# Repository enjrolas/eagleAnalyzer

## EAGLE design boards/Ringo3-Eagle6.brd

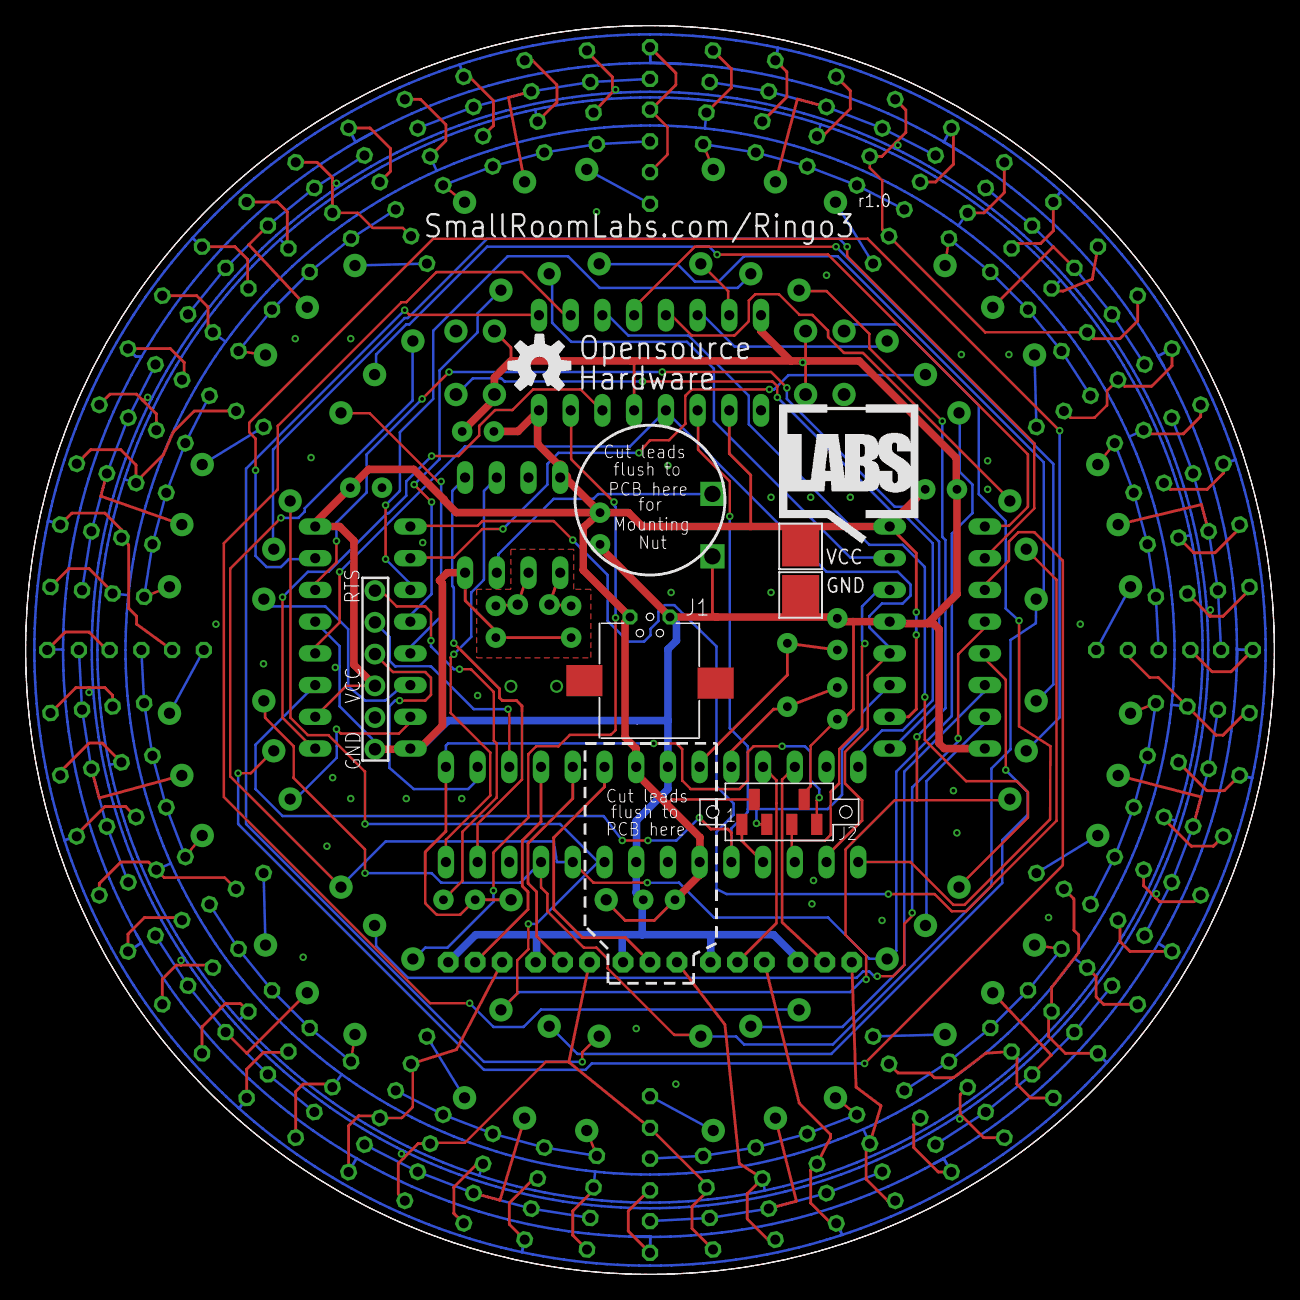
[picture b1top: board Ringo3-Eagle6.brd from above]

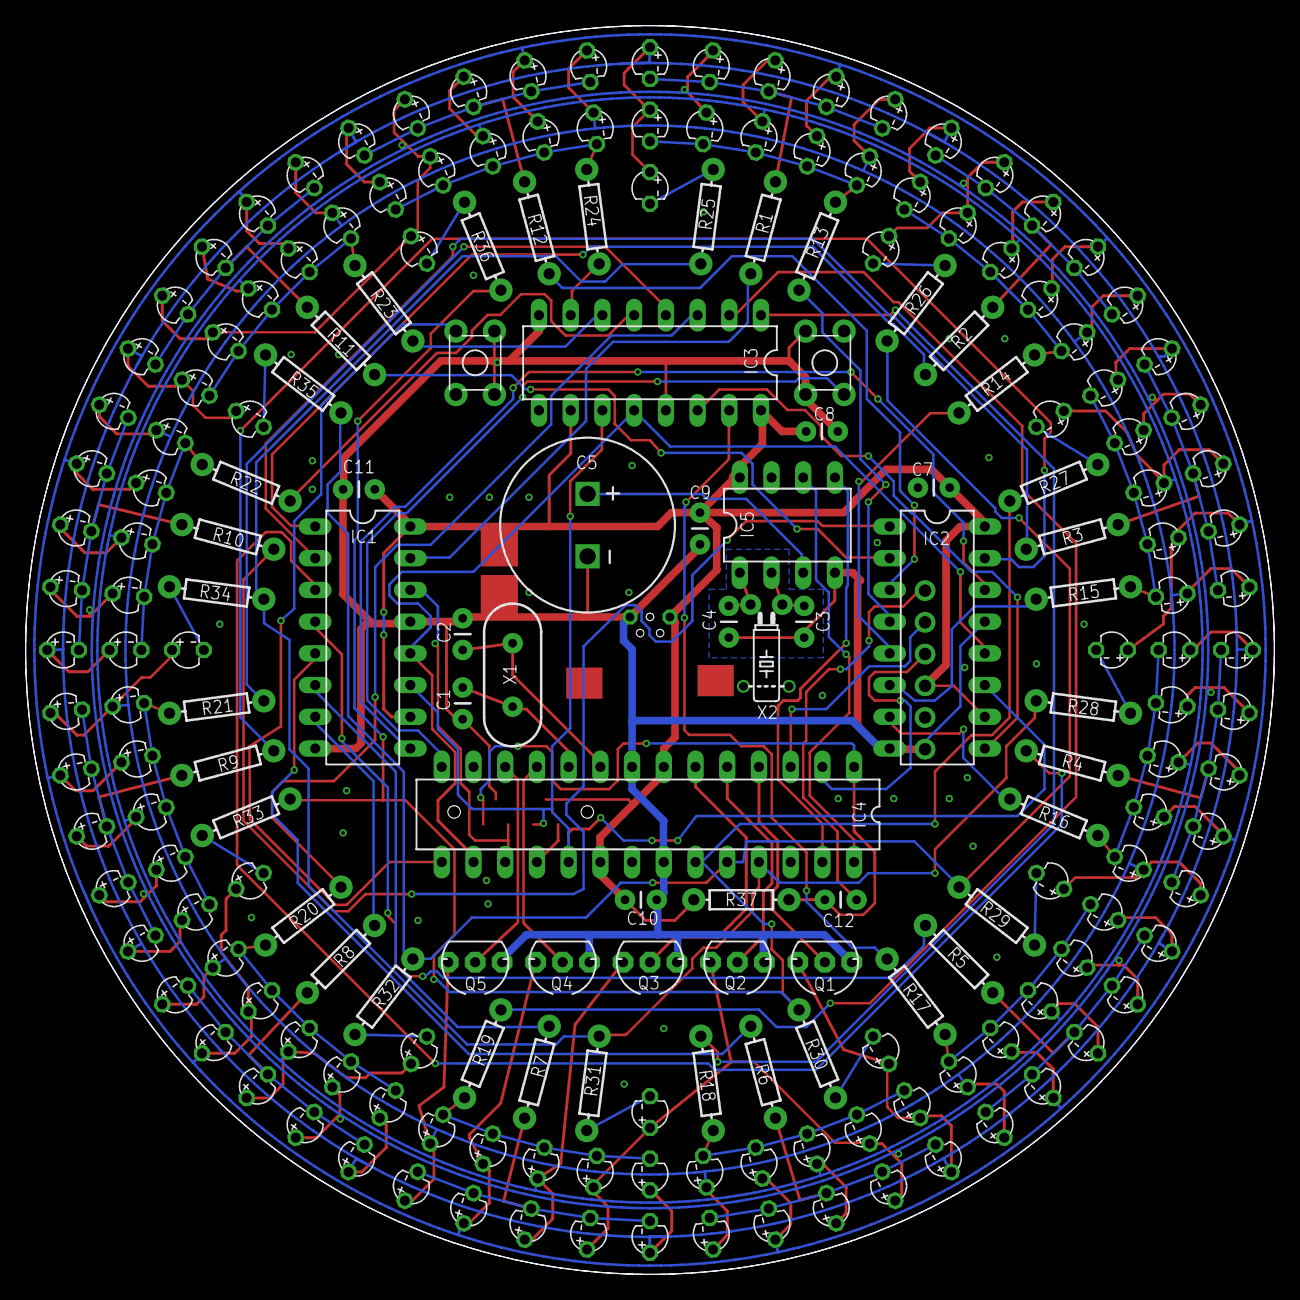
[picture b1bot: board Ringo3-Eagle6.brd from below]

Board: 2 copper layers, 100.0 x 100.0 mm, 199 parts (194 on the bottom side), 94 nets.

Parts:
C1, C2, C3, C4, C7, C8, C9, C10, C11, C12: CAP-PTH-SMALL
C5: CAPPOLSUPER13/5; CAP-SUPER13/5
CN1: 1X06_ROUND
D1, D2, D3, D4, D5, D6, D7, D8, D9, D10, D11, D12, D13, D14, D15, D16, D17, D18, D19, D20, D21, D22, D23, D24, D25, D26, D27, D28, D29, D30, D31, D32, D33, D34, D35, D36, D37, D38, D39, D40, D41, D42, D43, D44, D45, D46, D47, D48, D49, D50, D51, D52, D53, D54, D55, D56, D57, D58, D59, D60, D61, D62, D63, D64, D65, D66, D67, D68, D69, D70, D71, D72, D73, D74, D75, D76, D77, D78, D79, D80, D81, D82, D83, D84, D85, D86, D87, D88, D89, D90, D91, D92, D93, D94, D95, D96, D97, D98, D99, D100, D101, D102, D103, D104, D105, D106, D107, D108, D109, D110, D111, D112, D113, D114, D115, D116, D117, D118, D119, D120, D121, D122, D123, D124, D125, D126, D127, D128, D129, D130, D131, D132: LED3MM
IC1, IC2, IC3: 74HCT595N; DIL16
IC4: MEGA8-P; DIL28-3
IC5: MCP79410DIL; DIL08-LONG
J1: USB-PWRPAD; USB-MINIB-PTH-PWR-PAD
J2: AVR-ISP6_TOUCH; ISP-TOUCH
Q1, Q2, Q3, Q4, Q5: N-FETSTR; TO92-STRAIGHT
R1, R2, R3, R4, R5, R6, R7, R8, R9, R10, R11, R12, R13, R14, R15, R16, R17, R18, R19, R20, R21, R22, R23, R24, R25, R26, R27, R28, R29, R30, R31, R32, R33, R34, R35, R36, R37: AXIAL-0.3
U$17, U$18: TACTILETACT-4.5X4.5-PTH; TACTILE-PTH-4.5X4.5
U$21: OSHW-LOGO-M
U$22: SRL-LOGO-SILK-10MM
X1: HC49US
X2: TC26H

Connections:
AN1: IC1.15, R1.P$1
AN2: IC1.1, R2.P$1
AN3: IC1.2, R3.P$1
AN4: IC1.3, R4.P$1
AN5: IC1.4, R5.P$1
AN6: IC1.5, R6.P$1
AN7: IC1.6, R7.P$1
AN8: IC1.7, R8.P$1
AN9: IC2.15, R9.P$1
AN10: IC2.1, R10.P$1
AN11: IC2.2, R11.P$1
AN12: IC2.3, R12.P$1
AN13: IC2.4, R13.P$1
AN14: IC2.5, R14.P$1
AN15: IC2.6, R15.P$1
AN16: IC2.7, R16.P$1
AN17: IC3.15, R17.P$1
AN18: IC3.1, R18.P$1
AN19: IC3.2, R19.P$1
AN20: IC3.3, R20.P$1
AN21: IC3.4, R21.P$1
AN22: IC3.5, R22.P$1
AN23: IC3.6, R23.P$1
AN24: IC3.7, R24.P$1
AN25: IC4.25, R25.P$1, R28.P$1, R31.P$1, R34.P$1
AN26: IC4.24, R26.P$1, R29.P$1, R32.P$1, R35.P$1
AN27: IC4.23, R27.P$1, R30.P$1, R33.P$1, R36.P$1
AVR-RX: CN1.4, IC4.2
AVR-TX: CN1.5, IC4.3
BUTTON1: IC4.14, U$17.2A
BUTTON2: IC4.15, U$18.2A
CA1: IC4.4, Q1.2
CA1-BUS: D1.A, D6.A, D11.A, D16.A, D21.A, D26.A, D31.A, D36.A, D41.A, D46.A, D51.A, D56.A, D61.A, D66.A, D71.A, D76.A, D81.A, D86.A, D91.A, D96.A, D101.A, D106.A, D111.A, D116.A, D121.A, D126.A, D131.A, Q1.3
CA2: IC4.5, Q2.2
CA2-BUS: D2.A, D7.A, D12.A, D17.A, D22.A, D27.A, D32.A, D37.A, D42.A, D47.A, D52.A, D57.A, D62.A, D67.A, D72.A, D77.A, D82.A, D87.A, D92.A, D97.A, D102.A, D107.A, D112.A, D117.A, D122.A, D127.A, D132.A, Q2.3
CA3: IC4.6, Q3.2
CA3-BUS: D3.A, D8.A, D13.A, D18.A, D23.A, D28.A, D33.A, D38.A, D43.A, D48.A, D53.A, D58.A, D63.A, D68.A, D73.A, D78.A, D83.A, D88.A, D93.A, D98.A, D103.A, D108.A, D113.A, D118.A, D123.A, D128.A, Q3.3
CA4: IC4.11, Q4.2
CA4-BUS: D4.A, D9.A, D14.A, D19.A, D24.A, D29.A, D34.A, D39.A, D44.A, D49.A, D54.A, D59.A, D64.A, D69.A, D74.A, D79.A, D84.A, D89.A, D94.A, D99.A, D104.A, D109.A, D114.A, D119.A, D124.A, D129.A, Q4.3
CA5: IC4.12, Q5.2
CA5-BUS: D5.A, D10.A, D15.A, D20.A, D25.A, D30.A, D35.A, D40.A, D45.A, D50.A, D55.A, D60.A, D65.A, D70.A, D75.A, D80.A, D85.A, D90.A, D95.A, D100.A, D105.A, D110.A, D115.A, D120.A, D125.A, D130.A, Q5.3
DATA1: IC1.9, IC2.14
DATA2: IC2.9, IC3.14
GND: C1.2, C2.2, C3.2, C4.2, C5.C, C7.2, C8.2, C9.2, C10.2, C11.2, CN1.1, IC1.8, IC1.13, IC2.8, IC2.13, IC3.8, IC3.13, IC4.8, IC4.22, IC5.4, J1.GND, J2.6, Q1.1, Q2.1, Q3.1, Q4.1, Q5.1, U$17.1A, U$17.1B, U$18.1A, U$18.1B
LATCH: IC1.12, IC2.12, IC3.12, IC4.16
MISO: IC4.18, J2.1
MOSI: IC1.14, IC4.17, J2.4
unnamed: D1.C, D2.C, D3.C, D4.C, D5.C, R1.P$2
unnamed: D6.C, D7.C, D8.C, D9.C, D10.C, R2.P$2
unnamed: D21.C, D22.C, D23.C, D24.C, D25.C, R5.P$2
unnamed: D26.C, D27.C, D28.C, D29.C, D30.C, R6.P$2
unnamed: D31.C, D32.C, D33.C, D34.C, D35.C, R7.P$2
unnamed: D36.C, D37.C, D38.C, D39.C, D40.C, R8.P$2
unnamed: D11.C, D12.C, D13.C, D14.C, D15.C, R3.P$2
unnamed: D16.C, D17.C, D18.C, D19.C, D20.C, R4.P$2
unnamed: D41.C, D42.C, D43.C, D44.C, D45.C, R9.P$2
unnamed: D46.C, D47.C, D48.C, D49.C, D50.C, R10.P$2
unnamed: D51.C, D52.C, D53.C, D54.C, D55.C, R11.P$2
unnamed: D56.C, D57.C, D58.C, D59.C, D60.C, R12.P$2
unnamed: D116.C, D117.C, D118.C, D119.C, D120.C, R24.P$2
unnamed: D111.C, D112.C, D113.C, D114.C, D115.C, R23.P$2
unnamed: D106.C, D107.C, D108.C, D109.C, D110.C, R22.P$2
unnamed: D101.C, D102.C, D103.C, D104.C, D105.C, R21.P$2
unnamed: D96.C, D97.C, D98.C, D99.C, D100.C, R20.P$2
unnamed: C3.1, IC5.2, X2.1
unnamed: D91.C, D92.C, D93.C, D94.C, D95.C, R19.P$2
unnamed: D86.C, D87.C, D88.C, D89.C, D90.C, R18.P$2
unnamed: D66.C, D67.C, D68.C, D69.C, D70.C, R14.P$2
unnamed: D71.C, D72.C, D73.C, D74.C, D75.C, R15.P$2
unnamed: D76.C, D77.C, D78.C, D79.C, D80.C, R16.P$2
unnamed: D81.C, D82.C, D83.C, D84.C, D85.C, R17.P$2
unnamed: D61.C, D62.C, D63.C, D64.C, D65.C, R13.P$2
unnamed: C4.1, IC5.1, X2.2
unnamed: C12.2, CN1.6
unnamed: C5.A, IC5.3
unnamed: D121.C, R25.P$2
unnamed: D122.C, R26.P$2
unnamed: D123.C, R27.P$2
unnamed: D124.C, R28.P$2
unnamed: D125.C, R29.P$2
unnamed: D126.C, R30.P$2
unnamed: D127.C, R31.P$2
unnamed: D128.C, R32.P$2
unnamed: D129.C, R33.P$2
unnamed: D130.C, R34.P$2
unnamed: D131.C, R35.P$2
unnamed: D132.C, R36.P$2
RESET: C12.1, IC4.1, J2.5, R37.P$2
SCK: IC1.11, IC2.11, IC3.11, IC4.19, J2.3
SCL: IC4.28, IC5.6
SDA: IC4.27, IC5.5
VCC: C7.1, C8.1, C9.1, C10.1, C11.1, CN1.3, IC1.10, IC1.16, IC2.10, IC2.16, IC3.10, IC3.16, IC4.7, IC4.20, IC5.8, J1.VBUS, J2.2, R37.P$1
XTAL1: C2.1, IC4.9, X1.2
XTAL2: C1.1, IC4.10, X1.1

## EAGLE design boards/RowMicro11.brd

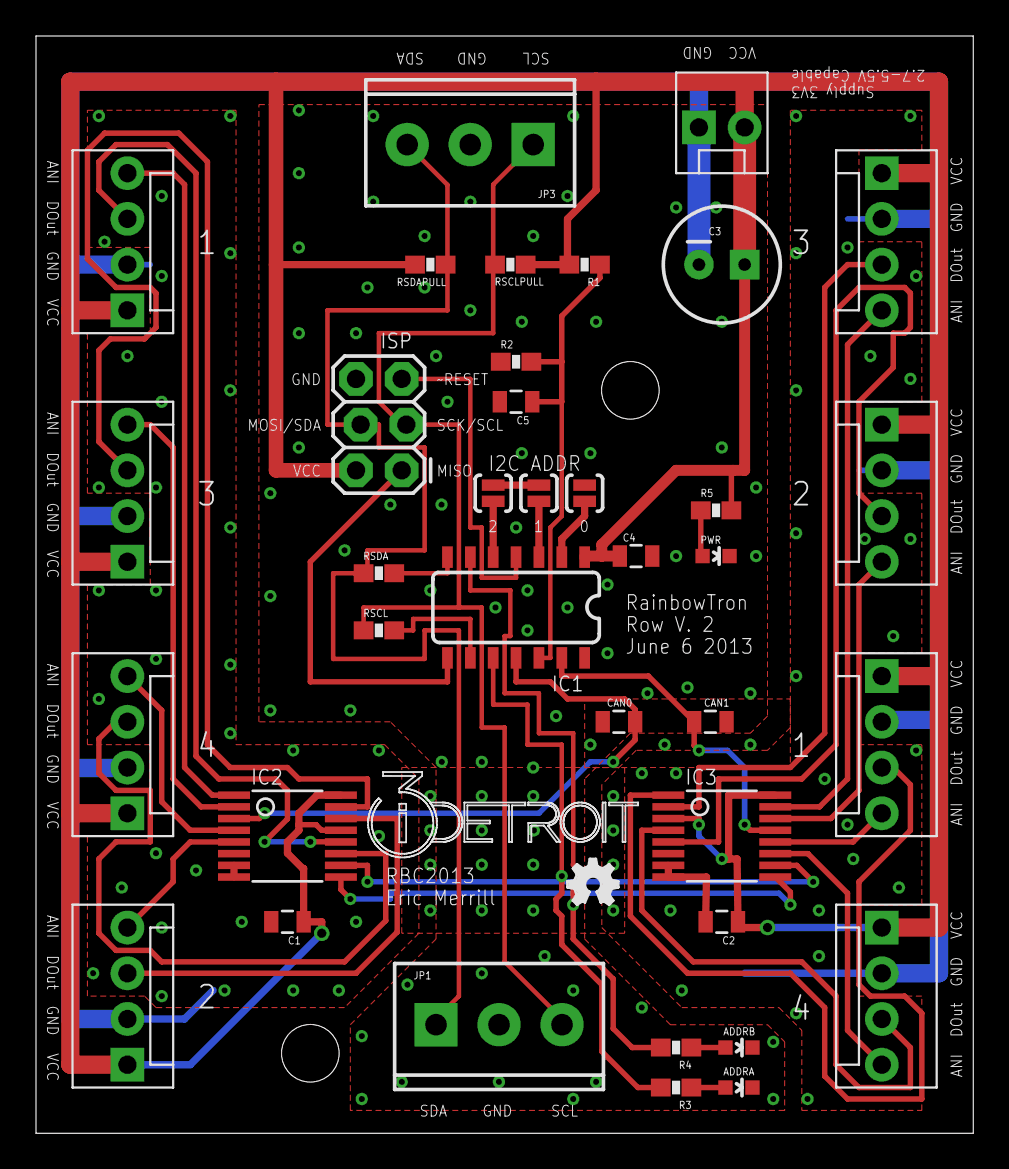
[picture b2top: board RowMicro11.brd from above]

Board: 2 copper layers, 52.1 x 61.0 mm, 39 parts (0 on the bottom side), 35 nets.

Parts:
ADDRA: LED-0603
ADDRB: LED-0603
C1, C2, C4: .1uF; 0805
C3: CPOL-RADIAL-100UF-25V
C5: 10uF; 0805
CAN0, CAN1: 1uF; 0805
IC1: ATTINY84; SO14
IC2, IC3: 74LV4052; TSSOP16L
ISP: 2X3_LOCK
JP1, JP3: SCREWTERMINAL-3.5MM-3
JP2: MOLEX-1X2
JP9, JP10, JP11, JP12, JP13, JP14, JP15, JP16: MOLEX-1X4
PWR: LED-0603
R1: 2.55kΩ; 0603-RES
R2: 5.1kΩ; 0603-RES
R3, R4, R5: 150Ω; 0603-RES
RSCL: 200Ω; 0603-RES
RSCLPULL: 0603-RES
RSDA: 200Ω; 0603-RES
RSDAPULL: 0603-RES
SJ3: 0; SJ_2S-NO
SJ4: 1; SJ_2S-NO
SJ5: 2; SJ_2S-NO
U$1: I3DETROITVEC15MM
U$2: OSHW_FILLX100_NOTEXT

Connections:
ADDRA: IC1.10, IC2.10, IC3.10, R3.2
ADDRB: IC1.6, IC2.9, IC3.9, R4.2
AIN_L1: IC2.1, JP9.4
AIN_L2: IC2.5, JP10.4
AIN_L3: IC2.2, JP11.4
AIN_L4: IC2.4, JP12.4
AIN_R1: IC3.12, JP13.4
AIN_R2: IC3.14, JP14.4
AIN_R3: IC3.15, JP15.4
AIN_R4: IC3.11, JP16.4
DOUT_L1: IC2.12, JP9.3
DOUT_L2: IC2.14, JP10.3
DOUT_L3: IC2.15, JP11.3
DOUT_L4: IC2.11, JP12.3
DOUT_R1: IC3.1, JP13.3
DOUT_R2: IC3.5, JP14.3
DOUT_R3: IC3.2, JP15.3
DOUT_R4: IC3.4, JP16.3
GND: ADDRA.C, ADDRB.C, C1.2, C2.2, C3.2, C4.2, C5.2, CAN0.2, CAN1.2, IC1.14, IC2.6, IC2.7, IC2.8, IC3.6, IC3.7, IC3.8, ISP.6, JP1.2, JP2.1, JP3.2, JP9.2, JP10.2, JP11.2, JP12.2, JP13.2, JP14.2, JP15.2, JP16.2, PWR.C, R2.1, SJ3.2, SJ4.2, SJ5.2
I2CADDR0: IC1.2, SJ3.1
I2CADDR1: IC1.3, SJ4.1
I2CADDR2: IC1.5, SJ5.1
MISO: IC1.8, ISP.1
unnamed: ADDRA.A, R3.1
unnamed: ADDRB.A, R4.1
unnamed: C5.1, IC1.12, R1.1, R2.2
unnamed: CAN0.1, IC1.11, IC2.3
unnamed: IC1.9, RSCL.2
unnamed: PWR.A, R5.1
unnamed: CAN1.1, IC1.13, IC3.13
unnamed: IC1.7, RSDA.2
RESET: IC1.4, ISP.5
SCL: ISP.3, JP1.3, JP3.1, RSCL.1, RSCLPULL.1
SDA: ISP.4, JP1.1, JP3.3, RSDA.1, RSDAPULL.1
VCC: C1.1, C2.1, C3.1, C4.1, IC1.1, IC2.13, IC2.16, IC3.3, IC3.16, ISP.2, JP2.2, JP9.1, JP10.1, JP11.1, JP12.1, JP13.1, JP14.1, JP15.1, JP16.1, R1.2, R5.2, RSCLPULL.2, RSDAPULL.2

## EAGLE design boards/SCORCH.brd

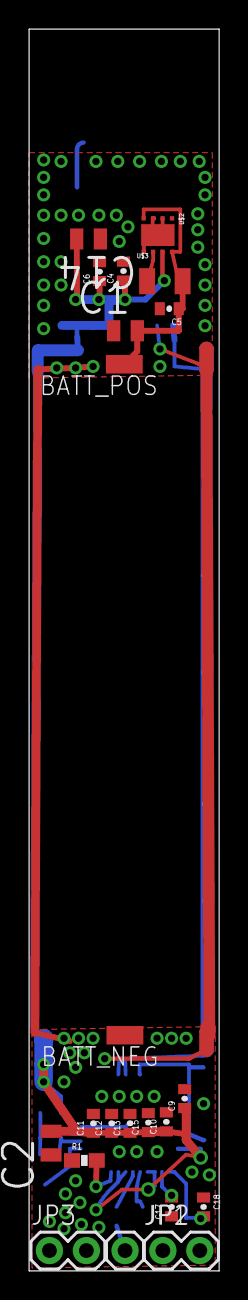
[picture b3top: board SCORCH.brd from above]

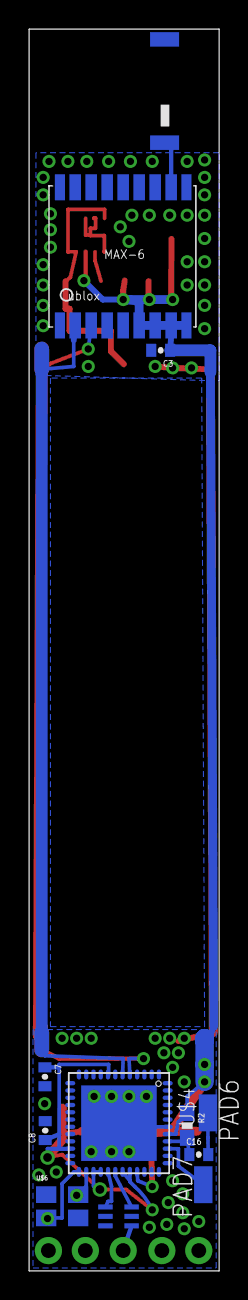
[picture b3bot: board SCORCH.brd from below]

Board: 2 copper layers, 13.1 x 85.4 mm, 34 parts (12 on the bottom side), 16 nets.

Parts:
BATT_NEG: SMD1,27-2,54
BATT_POS: SMD1,27-2,54
C1, C2, C14: 22uF; CAPC2013X90N
C3: 100n; 0402-CAP
C4, C5, C6, C7, C8, C9, C10, C11, C12, C13, C15: 100nF; 0402-CAP
C16: 2.2n; 0402-CAP
C17, C18: 12pF; 0402-CAP
JP1: M01PTH; 1X01
JP2, JP3: 1X02
PAD6, PAD7: WIREPADSMD1,27-254; SMD1,27-2,54
R1: 56K; 0603-RES
R2: 47K; 0603-RES
U$1: UBLOX_MAX-6
U$2: MAX1947MAX1947; 8QFN
U$3: SPM6530SPM6530; INDUCTOR
U$4: CC430F513X---RGZ48; RGZ48
U$5: BALUN433; BALUN
U$6: XTAL26A26; XTAL26
U$7: JTI_ANTENNA-1575AT43A40

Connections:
BATT: BATT_POS.1, C1.2, C5.1, U$2.4, U$2.8, U$3.2
FRM_GPS: U$1.2_TXD1, U$4.6
GND: BATT_NEG.1, C1.1, C2.1, C3.2, C4.2, C5.2, C6.2, C7.2, C8.2, C9.2, C10.2, C11.2, C12.2, C13.2, C14.1, C15.2, C17.1, C18.1, JP2.1, JP2.2, JP3.1, JP3.2, R1.1, U$1.1_GND, U$1.10_GND, U$1.12_GND, U$2.2, U$2.3, U$2.5, U$2.9, U$4.42, U$4.TP, U$5.2, U$5.5, U$5.6, U$6.2, U$6.4
unnamed: U$4.29, U$5.4
unnamed: U$4.30, U$5.3
unnamed: C16.1, R2.2, U$4.40
unnamed: C17.2, U$4.26, U$6.1
unnamed: C18.2, U$4.25, U$6.3
unnamed: R1.2, U$4.33
unnamed: U$2.6, U$3.1
unnamed: U$1.11_RF_IN, U$7.FEED
unnamed: PAD7.1, U$4.39
unnamed: C16.2, PAD6.1
RF_OUT: JP1.1, U$5.1
TO_GPS: U$1.3_RXD1, U$4.5
VCC: C2.2, C3.1, C4.1, C6.1, C7.1, C8.1, C9.1, C10.1, C11.1, C12.1, C13.1, C14.2, C15.1, R2.1, U$1.6_V_BCKP, U$1.7_VCC_IO, U$1.8_VCC, U$1.9_V_RESET, U$2.7, U$4.8, U$4.22, U$4.27, U$4.28, U$4.31, U$4.32, U$4.41

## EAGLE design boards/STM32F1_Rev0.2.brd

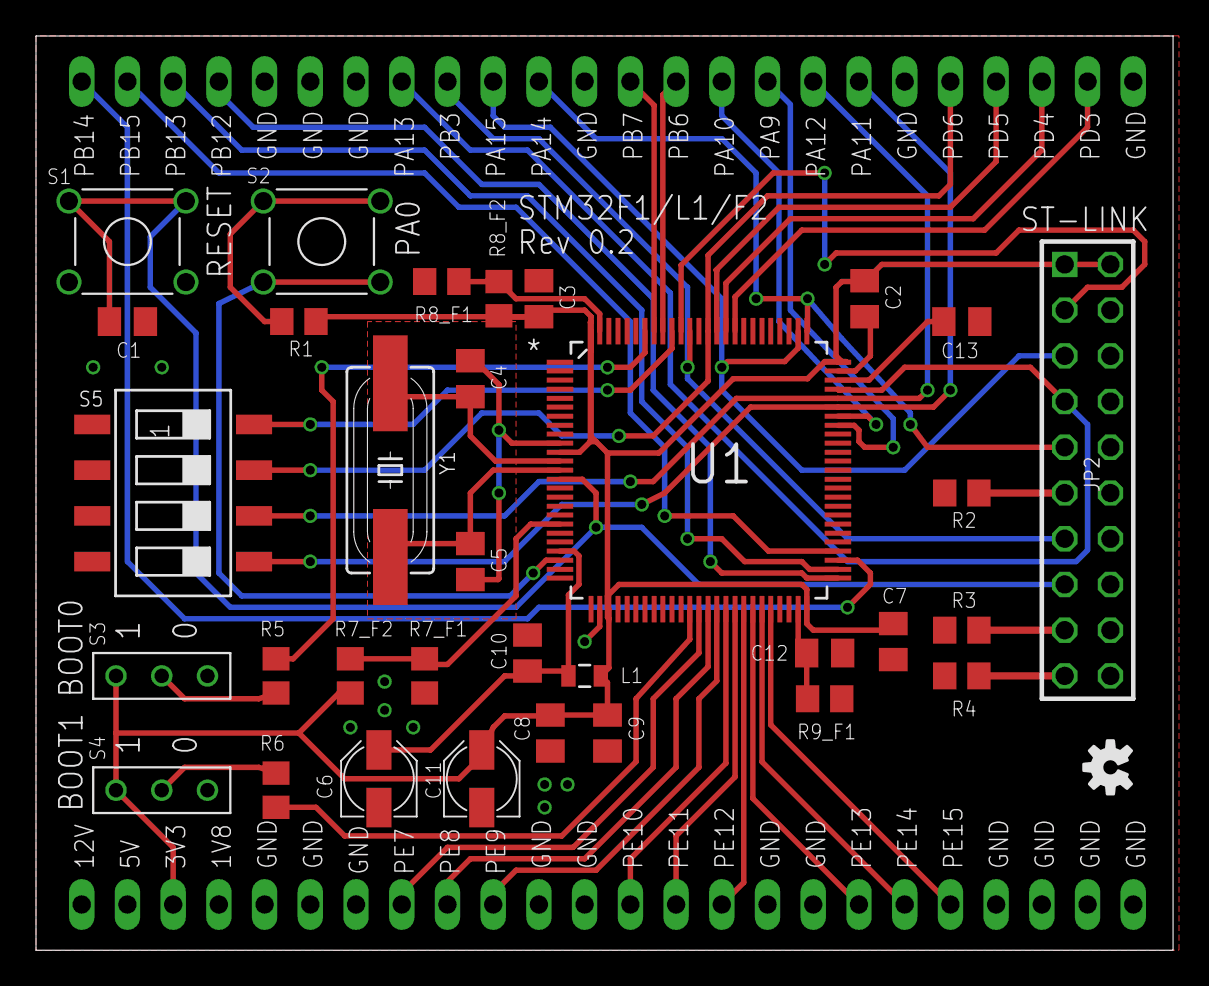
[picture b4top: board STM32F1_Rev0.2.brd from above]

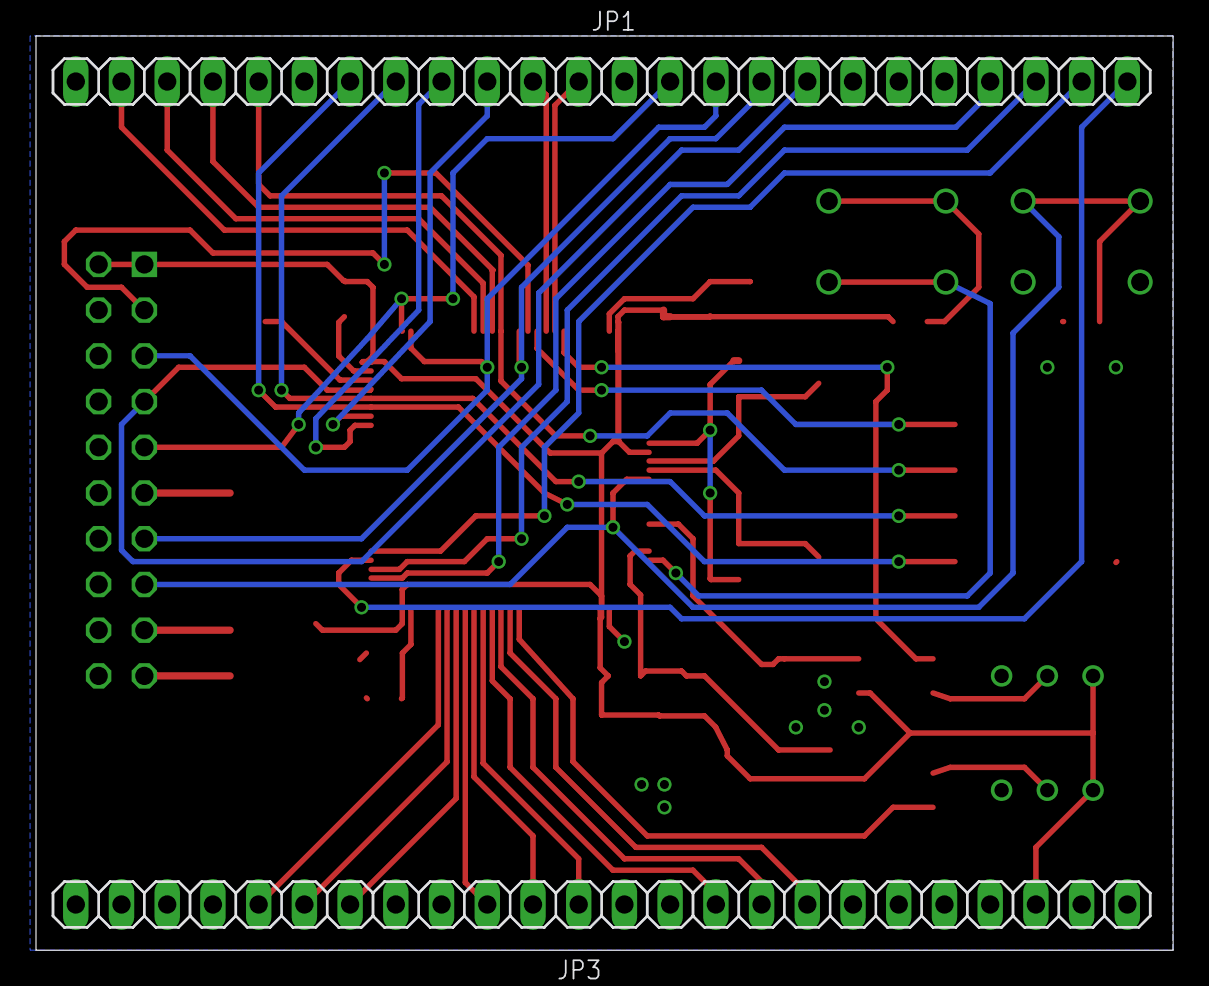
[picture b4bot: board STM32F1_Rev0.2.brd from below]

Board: 2 copper layers, 63.2 x 50.8 mm, 36 parts (2 on the bottom side), 48 nets.

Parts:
C1: 10nF; C0805K
C2, C3, C7, C8, C9, C10, C12, C13: 100nF; C0805K
C4, C5: 20pF; C0805K
C6: 1uF; PANASONIC_B
C11: 10uF; PANASONIC_B
JP1, JP3: 1X24
JP2: 2X10
L1: 470 Ohm@100MHz; 0805
R1, R2, R3, R4, R5, R6: 10K; R0805
R7_F1, R7_F2, R8_F1, R8_F2, R9_F1: 0; R0805
S1, S2: SWITCH_TH; SWITCH_TROUGHHOLE
S3, S4: SS12SDXX
S5: SWS004; SMS-004
U1: STM32L152VBT6; QFP50P1600X1600X160-100N
U$1: OSHW-LOGOS; OSHW-LOGO-S
Y1: 8MHz; HC49UP

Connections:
3.3V: C2.1, C3.1, C7.1, C8.1, C9.1, C11.+, JP2.1, JP2.2, JP3.3, L1.1, R1.2, R7_F2.1, R8_F2.1, S3.3, S4.3, U1.11, U1.28, U1.50, U1.75, U1.100
!SPI_SS: JP1.4, U1.51
!UART1_CTS: JP1.18, S5.5, U1.70
!UART1_RTS: JP1.17, S5.6, U1.71
!UART2_CTS: JP1.23, U1.84
!UART2_RTS: JP1.22, U1.85
BOOT0: R5.2, U1.94
BOOT1: R6.2, U1.37
GND: C1.2, C2.2, C3.2, C4.2, C5.2, C6.-, C7.2, C8.2, C9.2, C10.2, C11.-, C12.2, C13.1, JP1.5, JP1.6, JP1.7, JP1.12, JP1.19, JP1.24, JP2.4, JP2.6, JP2.8, JP2.10, JP2.12, JP2.14, JP2.16, JP2.18, JP2.20, JP3.5, JP3.6, JP3.7, JP3.11, JP3.12, JP3.16, JP3.17, JP3.21, JP3.22, JP3.23, JP3.24, R2.1, R3.1, R4.1, R7_F1.2, R8_F1.2, R9_F1.2, S1.3, S1.4, S3.1, S4.1, S5.1, S5.2, S5.3, S5.4, U1.10, U1.27, U1.74
I2C_SCL: JP1.14, U1.92
I2C_SDA: JP1.13, U1.93
JTAG_TCK: JP1.11, JP2.9, U1.76
JTAG_TDI: JP1.10, JP2.5, U1.77
JTAG_TDO: JP1.9, JP2.13, U1.89
JTAG_TMS: JP1.8, JP2.7, U1.72
unnamed: C13.2, U1.73
unnamed: C6.+, C10.1, L1.2, U1.22
unnamed: R1.1, S2.1, S2.2
unnamed: R5.1, S3.2
unnamed: R6.1, S4.2
unnamed: JP2.11, R2.2
unnamed: JP2.17, R3.2
unnamed: JP2.19, R4.2
OSCI: C4.1, U1.12, Y1.1
OSCO: C5.1, U1.13, Y1.2
PA0: S2.3, S2.4, U1.23
PB5: S5.8, U1.91
RESET#: C1.1, JP2.15, S1.1, S1.2, U1.14
RFU: R8_F1.1, R8_F2.2, U1.99
SPI_SCK: JP1.3, U1.52
SPI_SDI: JP1.1, U1.53
SPI_SDO: JP1.2, U1.54
TRST: JP2.3, U1.90
UART1_RX: JP1.15, U1.69
UART1_TX: JP1.16, U1.68
UART2_RX: JP1.20, S5.7, U1.87
UART2_TX: JP1.21, U1.86
USER_BTN1: JP3.18, U1.44
USER_BTN2: JP3.19, U1.45
USER_BTN3: JP3.20, U1.46
USER_GPIO1: JP3.8, U1.38
USER_GPIO2: JP3.9, U1.39
USER_GPIO3: JP3.10, U1.40
USER_LED1: JP3.13, U1.41
USER_LED2: JP3.14, U1.42
USER_LED3: JP3.15, U1.43
VSS1: C12.1, R9_F1.1, U1.49
VSSA: R7_F1.1, R7_F2.2, U1.19

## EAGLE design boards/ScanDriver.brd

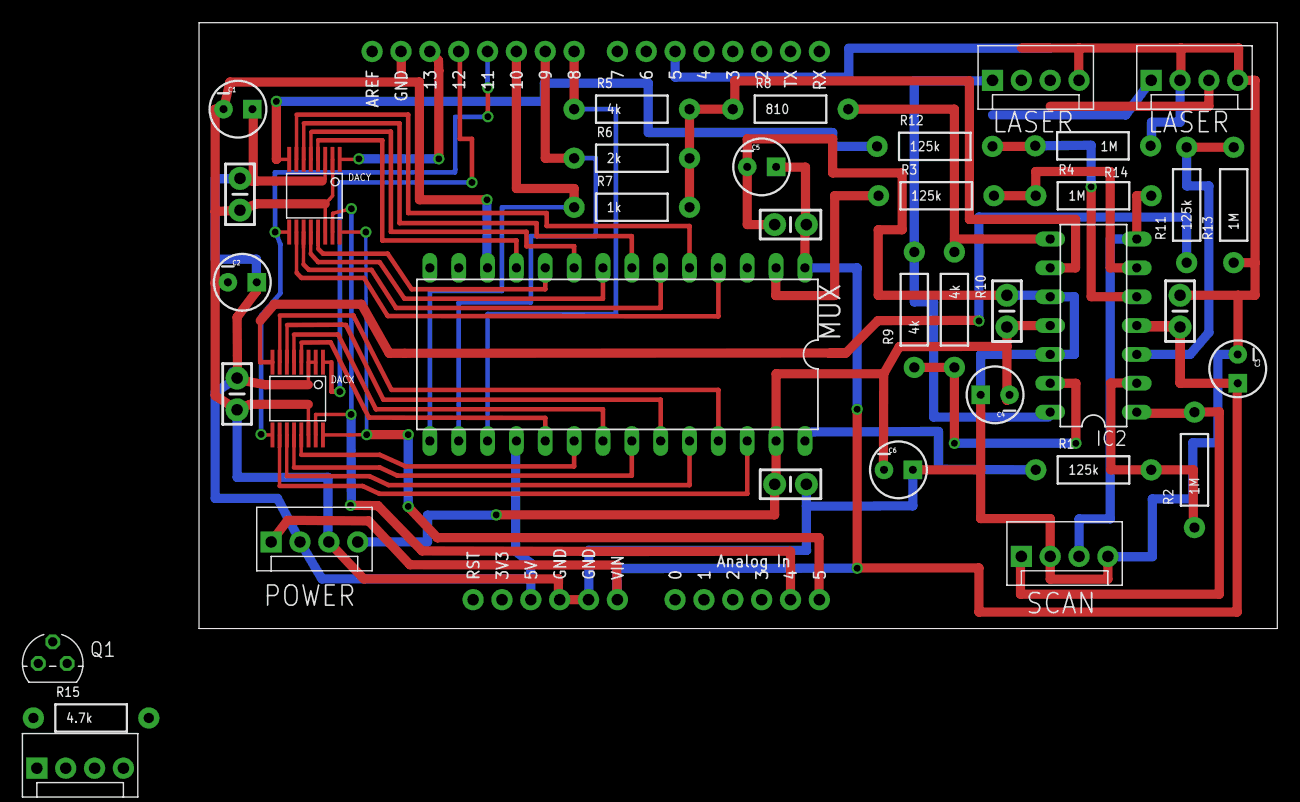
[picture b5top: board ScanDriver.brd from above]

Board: 2 copper layers, 94.9 x 53.3 mm, 38 parts (0 on the bottom side), 49 nets.

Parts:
C1, C2, C3, C4, C5, C6: 10uF; CPOL-RADIAL-10UF-25V
C7, C8, C9, C10, C11, C12: .1uF; CAP-PTH-SMALL-KIT
DACX: AD5669R; SSOP16
DACY: AD5669R; SSOP16
IC2: OPA404P; DIL14
JP1: Power; MOLEX-1X4
JP2: ScanOut; MOLEX-1X4
JP3: LASER; MOLEX-1X4
JP4: SYNC; MOLEX-1X4
JP5: THERM; MOLEX-1X4
MUX: ADG507A; DIL28-6
Q1: 2N3904; TO92
R1, R3, R11, R12: 125k; AXIAL-0.4
R2, R4, R13, R14: 1M; AXIAL-0.4
R5, R9, R10: 4k; AXIAL-0.4
R6: 2k; AXIAL-0.4
R7: 1k; AXIAL-0.4
R8: 810; AXIAL-0.4
R15: 4.7k; AXIAL-0.4
U1: ARDUINO_SHIELDNOHOLES; DUEMILANOVE_SHIELD_NOHOLES

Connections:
+5V: C1.1, C2.1, C7.2, C8.2, DACX.P$2, DACX.P$3, DACY.P$3, JP1.2, MUX.18, Q1.1, R15.P$2, U1.5V
+12V: C3.1, C5.1, C9.2, C11.2, IC2.4, JP1.1, MUX.1, U1.VIN
-12V: C4.2, C6.2, C10.2, C12.2, IC2.11, JP1.4, MUX.27
A0: MUX.17, R5.P$1, U1.D8
A1: MUX.16, R6.P$1, U1.D9
A2: MUX.15, R7.P$1, U1.D10
ADDROUT: IC2.14, JP3.1, R9.P$2
CLR: DACX.P$9, DACY.P$9, U1.D11
DACSYNC: JP4.2, U1.D4
GND: C1.2, C2.2, C3.2, C4.1, C5.2, C6.1, C7.1, C8.1, C9.1, C10.1, C11.1, C12.1, DACX.P$14, DACY.P$2, DACY.P$14, IC2.10, IC2.12, JP1.3, JP2.2, JP2.4, JP3.2, JP3.4, JP5.2, JP5.3, JP5.4, MUX.12, R13.P$1, R14.P$1, U1.GND@0, U1.GND@1, U1.GND@2
LASERCMD: JP3.3, U1.D5
unnamed: IC2.2, R1.P$2, R2.P$1
unnamed: IC2.6, R3.P$2, R4.P$1
unnamed: IC2.9, R5.P$2, R6.P$2, R7.P$2, R8.P$1
unnamed: IC2.8, R8.P$2, R10.P$1
unnamed: IC2.13, R9.P$1, R10.P$2
unnamed: IC2.3, R11.P$2, R13.P$2
unnamed: IC2.5, R12.P$2, R14.P$2
ONEWIRE: JP5.1, Q1.3, R15.P$1, U1.A0
ONEWIREPULLUP: Q1.2, U1.A1
SCL: DACX.P$16, DACY.P$16, U1.A5
SDA: DACX.P$15, DACY.P$15, U1.A4
SERIALSYNC: JP4.1, U1.D3
SWITCHEDX: MUX.28, R1.P$1
SWITCHEDY: MUX.2, R3.P$1
SYNC1: JP4.3, U1.D6
SYNC2: JP4.4, U1.D7
XLDAC: DACX.P$1, U1.D12
XOUT: IC2.1, JP2.1, R2.P$2
XREF: DACX.P$8, R11.P$1
XVA: DACX.P$4, MUX.19
XVB: DACX.P$13, MUX.20
XVC: DACX.P$5, MUX.21
XVD: DACX.P$12, MUX.22
XVE: DACX.P$6, MUX.23
XVF: DACX.P$11, MUX.24
XVG: DACX.P$7, MUX.25
XVH: DACX.P$10, MUX.26
YLDAC: DACY.P$1, U1.D13
YOUT: IC2.7, JP2.3, R4.P$2
YREF: DACY.P$8, R12.P$1
YVA: DACY.P$4, MUX.11
YVB: DACY.P$13, MUX.10
YVC: DACY.P$5, MUX.9
YVD: DACY.P$12, MUX.8
YVE: DACY.P$6, MUX.7
YVF: DACY.P$11, MUX.6
YVG: DACY.P$7, MUX.5
YVH: DACY.P$10, MUX.4

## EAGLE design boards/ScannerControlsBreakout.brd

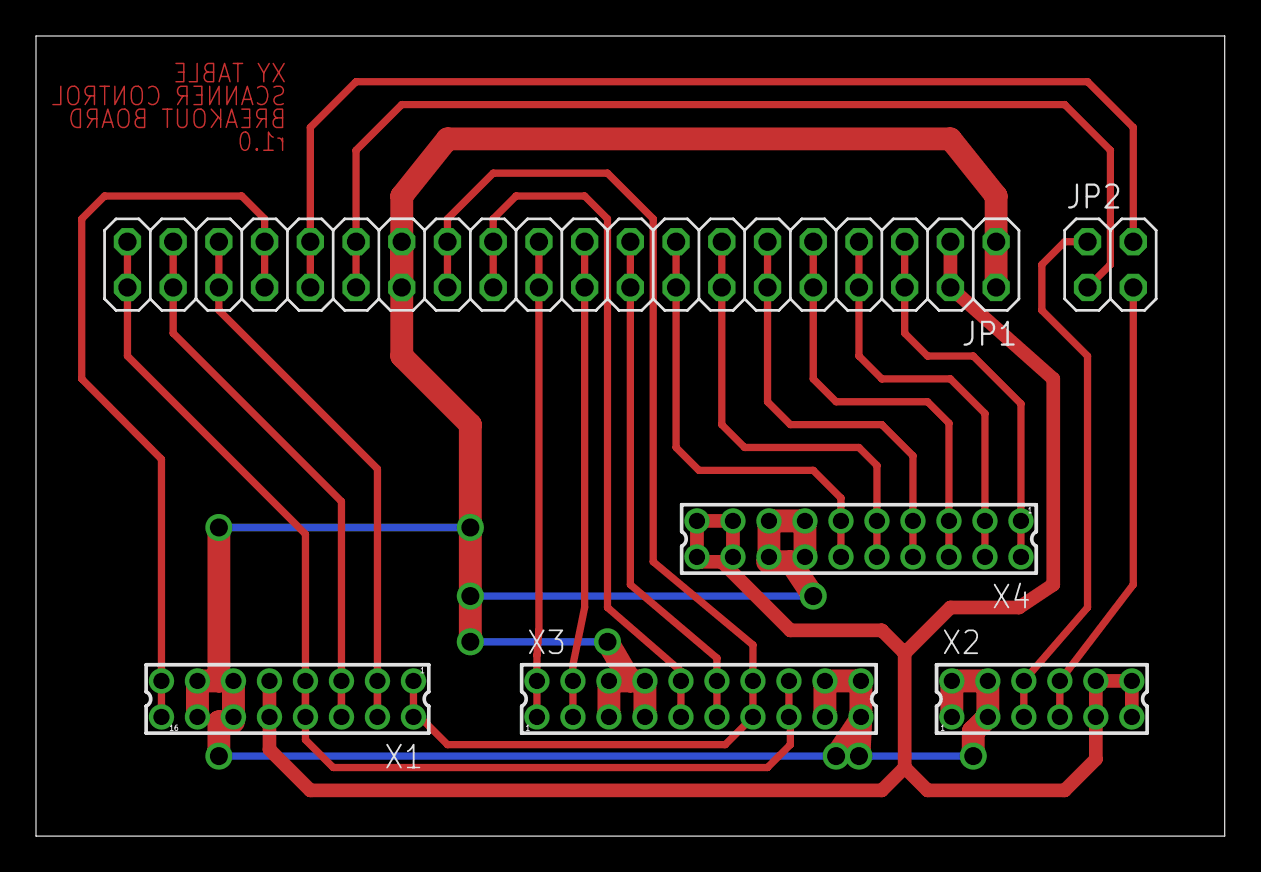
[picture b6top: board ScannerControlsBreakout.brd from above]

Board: 2 copper layers, 66.0 x 44.5 mm, 6 parts (0 on the bottom side), 21 nets.

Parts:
JP1: 2X20
JP2: 2X02
X1: 332-16
X2: 332-12
X3, X4: 332-20

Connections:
+5V: JP1.3, JP1.4, X1.9, X1.10, X2.9, X2.10, X2.11, X2.12, X4.17, X4.18, X4.19, X4.20
DOWN: JP1.35, JP1.36, X1.3, X1.4
GND: JP1.1, JP1.2, JP1.27, JP1.28, X1.11, X1.12, X1.13, X1.14, X2.1, X2.2, X2.3, X2.4, X3.5, X3.6, X3.7, X3.8, X3.17, X3.18, X3.19, X3.20, X4.13, X4.14, X4.15, X4.16
LEFT: JP1.25, JP1.26, X1.1, X1.2, X3.13, X3.14
unnamed: JP2.3, X2.7, X2.8
unnamed: JP1.15, JP1.16, X4.11, X4.12
unnamed: JP1.13, JP1.14, X4.9, X4.10
unnamed: JP1.11, JP1.12, X4.7, X4.8
unnamed: JP1.7, JP1.8, X4.3, X4.4
unnamed: JP1.31, JP1.32, JP2.4
unnamed: JP1.29, JP1.30, JP2.1
unnamed: JP2.2, X2.5, X2.6
unnamed: JP1.21, JP1.22, X3.1, X3.2
unnamed: JP1.19, JP1.20, X3.3, X3.4
unnamed: JP1.23, JP1.24, X3.9, X3.10
unnamed: JP1.17, JP1.18, X3.11, X3.12
unnamed: JP1.5, JP1.6, X4.1, X4.2
unnamed: JP1.9, JP1.10, X4.5, X4.6
RIGHT: JP1.39, JP1.40, X1.7, X1.8, X3.15, X3.16
RST: JP1.33, JP1.34, X1.15, X1.16
UP: JP1.37, JP1.38, X1.5, X1.6

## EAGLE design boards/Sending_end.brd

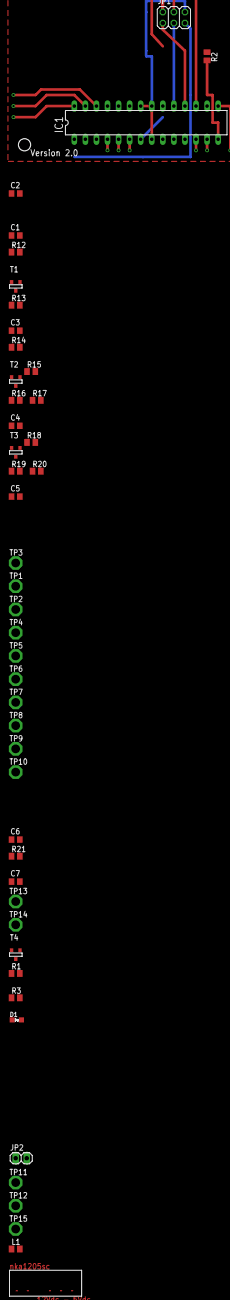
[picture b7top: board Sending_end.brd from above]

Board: 2 copper layers, 45 parts (0 on the bottom side), 34 nets.

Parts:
C1, C2, C3, C4, C5, C6, C7: C0805
D1: HSMXC670
IC1: MEGA8-P; DIL28-3
JP1: 2X03
JP2: 1X02
L1: tbd; M0805
R1, R2, R3, R12, R13, R14, R15, R16, R17, R18, R19, R20: tbd; M0805
R21: 10k; M0805
T1, T2, T3, T4: SOT-23
TP1, TP2, TP3, TP4, TP5, TP6, TP7, TP8, TP9, TP10, TP11, TP12, TP13, TP14, TP15: PTR1PAD1-20; P1-20
U$1: NKA1205SC

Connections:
GND: C1.2, C2.2, C3.2, C4.2, C5.2, C6.2, C7.2, D1.K, IC1.8, IC1.21, IC1.22, JP1.6, R1.1, R13.1, R16.1, R19.1, T1.2, T2.2, T3.2, U$1.-VOUT
unnamed: IC1.5, TP5.TP
unnamed: R1.2, R2.1, T4.3
unnamed: R3.1, T4.1
unnamed: IC1.2, TP2.TP
unnamed: D1.A, T4.2
unnamed: IC1.1, JP1.5, R21.2
unnamed: L1.2, U$1.+VOUT
unnamed: C3.1, R13.2, R14.2, T1.3
unnamed: IC1.9, TP1.TP
unnamed: IC1.28, R18.2, T3.1
unnamed: IC1.3, TP4.TP
unnamed: IC1.4, TP7.TP
unnamed: IC1.6, TP6.TP
unnamed: IC1.12, TP9.TP
unnamed: IC1.13, TP10.TP
unnamed: IC1.14, R2.2
unnamed: IC1.15, TP13.TP
unnamed: IC1.16, TP14.TP
unnamed: IC1.17, JP1.4
unnamed: IC1.18, JP1.1
unnamed: IC1.19, JP1.3
unnamed: JP2.2, U$1.-VIN
unnamed: IC1.23, TP11.TP
unnamed: IC1.24, TP12.TP
unnamed: IC1.25, TP15.TP
unnamed: JP2.1, U$1.+VIN
unnamed: C4.1, R16.2, R17.2, T2.3
unnamed: IC1.27, R15.2, T2.1
unnamed: C5.1, R19.2, R20.2, T3.3
unnamed: IC1.10, TP3.TP
unnamed: IC1.11, TP8.TP
unnamed: IC1.26, R12.2, T1.1
VCC: C1.1, C2.1, C6.1, C7.1, IC1.7, IC1.20, JP1.2, L1.1, R3.2, R12.1, R15.1, R18.1, R21.1

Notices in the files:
parts and their libraries:
SparkFun-Connectors: Licensing: CC v3.0 Share-Alike You are welcome to use this library for commercial purposes.
